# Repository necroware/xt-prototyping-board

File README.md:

# XT Prototyping Board

This board can be used to make prototypes for XT (8-bit ISA) slots.

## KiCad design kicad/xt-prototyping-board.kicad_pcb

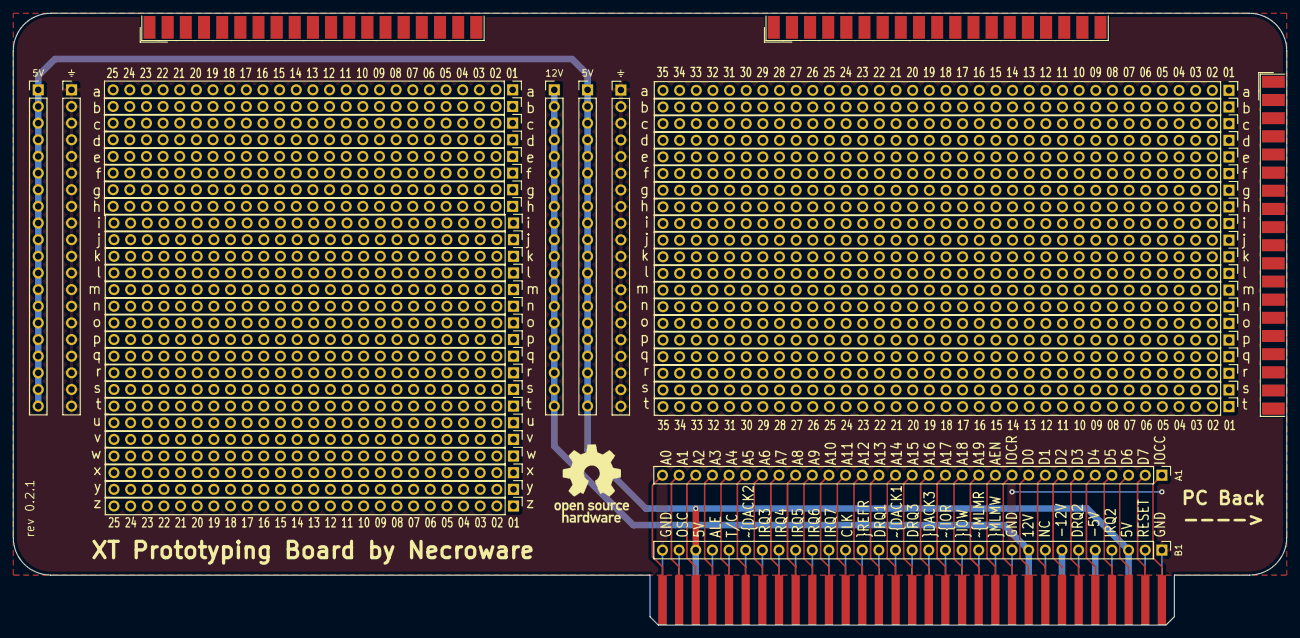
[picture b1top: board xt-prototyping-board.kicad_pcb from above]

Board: 2 copper layers, 194.3 x 93.3 mm, 8 parts (0 on the bottom side), 59 nets.

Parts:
A1: Conn_01x31; PinHeader_1x31_P2.54mm_Vertical
B1: Conn_01x31; PinHeader_1x31_P2.54mm_Vertical
I1: Bus_ISA_8bit; ISA_8BIT_EDGE
V1, V2, V3, V4, V5: Conn_01x20; PinHeader_1x20_P2.54mm_Vertical

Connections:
5V: B1.3, B1.29, I1.3, I1.29, V1.1, V1.2, V1.3, V1.4, V1.5, V1.6, V1.7, V1.8, V1.9, V1.10, V1.11, V1.12, V1.13, V1.14, V1.15, V1.16, V1.17, V1.18, V1.19, V1.20, V2.1, V2.2, V2.3, V2.4, V2.5, V2.6, V2.7, V2.8, V2.9, V2.10, V2.11, V2.12, V2.13, V2.14, V2.15, V2.16, V2.17, V2.18, V2.19, V2.20
12V: B1.9, I1.9, V5.1, V5.2, V5.3, V5.4, V5.5, V5.6, V5.7, V5.8, V5.9, V5.10, V5.11, V5.12, V5.13, V5.14, V5.15, V5.16, V5.17, V5.18, V5.19, V5.20
-5V: B1.5, I1.5
-12V: B1.7, I1.7
GND: B1.1, B1.10, B1.31, I1.1, I1.10, I1.31, V3.1, V3.2, V3.3, V3.4, V3.5, V3.6, V3.7, V3.8, V3.9, V3.10, V3.11, V3.12, V3.13, V3.14, V3.15, V3.16, V3.17, V3.18, V3.19, V3.20, V4.1, V4.2, V4.3, V4.4, V4.5, V4.6, V4.7, V4.8, V4.9, V4.10, V4.11, V4.12, V4.13, V4.14, V4.15, V4.16, V4.17, V4.18, V4.19, V4.20
unnamed: A1.1, I1.32
unnamed: A1.2, I1.33
unnamed: A1.3, I1.34
unnamed: A1.4, I1.35
unnamed: A1.5, I1.36
unnamed: A1.6, I1.37
unnamed: A1.7, I1.38
unnamed: A1.8, I1.39
unnamed: A1.9, I1.40
unnamed: A1.10, I1.41
unnamed: A1.11, I1.42
unnamed: A1.12, I1.43
unnamed: A1.13, I1.44
unnamed: A1.14, I1.45
unnamed: A1.15, I1.46
unnamed: A1.16, I1.47
unnamed: A1.17, I1.48
unnamed: A1.18, I1.49
unnamed: A1.19, I1.50
unnamed: A1.20, I1.51
unnamed: A1.21, I1.52
unnamed: A1.22, I1.53
unnamed: A1.23, I1.54
unnamed: A1.24, I1.55
unnamed: A1.25, I1.56
unnamed: A1.26, I1.57
unnamed: A1.27, I1.58
unnamed: A1.28, I1.59
unnamed: A1.29, I1.60
unnamed: A1.30, I1.61
unnamed: A1.31, I1.62
unnamed: B1.2, I1.2
unnamed: B1.4, I1.4
unnamed: B1.6, I1.6
unnamed: B1.8, I1.8
unnamed: B1.11, I1.11
unnamed: B1.12, I1.12
unnamed: B1.13, I1.13
unnamed: B1.14, I1.14
unnamed: B1.15, I1.15
unnamed: B1.16, I1.16
unnamed: B1.17, I1.17
unnamed: B1.18, I1.18
unnamed: B1.19, I1.19
unnamed: B1.20, I1.20
unnamed: B1.21, I1.21
unnamed: B1.22, I1.22
unnamed: B1.23, I1.23
unnamed: B1.24, I1.24
unnamed: B1.25, I1.25
unnamed: B1.26, I1.26
unnamed: B1.27, I1.27
unnamed: B1.28, I1.28
unnamed: B1.30, I1.30

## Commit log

2021-01-16 Initial version (rev 0.2)
2021-01-16 Add isa pin id text on the back
2021-01-16 Minor silk layer fixes
2021-01-16 Add readme and images
2021-01-19 Fix silk layer, now proper low active symbols
2021-01-26 Update images
2021-02-23 Fix library path
2021-02-23 Take OSHW Icon from Kicad std lib
